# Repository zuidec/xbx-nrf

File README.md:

# XBX-NRF

A replacement bottom board for the **Xbox Series X|S controller (model 1914)**
built on a Nordic **nRF52840**. Uses a custom **2.4 GHz USB dongle** instead of 
Xbox Wireless / Bluetooth for improved connectivity. 

> **Status:** Hardware Rev 1.1 up and running. Still in active development.
> Open tasks: [todo.md](todo.md).

## Who is this for

This is for those of us who love the Xbox controller's shape but hate how bad 
the Bluetooth connectivity is. This started as a labor of love for my partner 
who can't find a controller she likes besides the Xbox controller but also can't 
stand the disconnects.

That being said, there are some real concessions. The most obvious is that the 
controller won't work with an Xbox anymore. Another concession is that support 
for the rechargeable battery packs, as well as the expansion and headphone ports 
was dropped.

- How to build the hardware:
    [Building the hardware](docs/hardware_assembly.md)
- Once you have hardware in hand:
    **[Getting started](docs/getting_started.md)**

## Architecture

```
┌─────────── Controller ───────────┐          ┌──── Dongle ────┐
│ Stock top board ─J3─ new board   │ 2.4 GHz  │ nRF52840 + USB │
│ buttons (PCAL6416)  nRF52840     │◀────────▶│ XInput / HID   │──▶ PC
│ power latch, boost  radio,       │   ESB    │ gamepad        │
│ USB-C, 2×AA input   sticks,      │          │                │
│                     triggers,    │          │                │
│                     rumble       │          │                │
└──────────────────────────────────┘          └────────────────┘
```

## Features

| Area | Feature |
|---|---|
| Target | Xbox Series X\|S Controller (model 1914)|
| Scope | New bottom board, stock top board, shell, triggers, motors reused |
| MCU | nRF52840 |
| Wireless | Nordic ESB 2.4 GHz. The project does **NOT** use Bluetooth! |
| Multiplayer | Up to 7 paired, 4 connected per dongle |
| Polling rate| 1 kHz with 1–2 controllers, 500 Hz with 3–4 |
| Dongle USB mode| HID gamepad (**1 player**) and XInput (**4 players**) |
| Battery | **AAs only** - basic rechargeables are OK, but no Play & Charge |
| Rumble | reuses all the stock motors, including triggers |
| Buttons | reuses stock with additional options for 2 AUX trigger switches and 4 paddles |
| Waking PC | Works in wireless AND wired mode! |
| Audio | None in v1 |
| Expansion port | None in v1 |

> [!WARNING]
> **Never put a bare Li-ion cell on the AA contacts**: The boost converter
> appears to pass that straight through and the nRF52840 is only rated to 
> **3.6v** in this configuration!
> ([docs/hardware.md](docs/hardware.md)).

## Hardware

The custom board replaces the stock bottom board in the controller. It plugs 
into the stock top board's 14-pin **J3** connector. This provides power rails, 
USB, I2C to the button expander, and Guide / Pair / power-hold signals.

| Doc | Covers |
|---|---|
| [docs/hardware.md](docs/hardware.md) | Top board power, J3 pinout, antennas, dongle pin map |
| [docs/pcal6416.md](docs/pcal6416.md) | Button expander: button map, registers |
| [docs/a3910.md](docs/a3910.md) | Rumble drivers: wiring, logic table |
| [docs/teardown.md](docs/teardown.md) | Test controller teardown: motor wires |

## Firmware

Built using the nRF Connect SDK. Version is pinned at v3.4.1 to ensure future 
buildability (hopefully). The controller firmware has a target for the custom 
board and the dongle firmware has a target for the custom dongle as well as the 
PCA10059 dongle. You may notice there is a nice!nano/pro-micro target for the 
controller, but this is just for testing.

| Doc | Covers |
|---|---|
| [docs/controller.md](docs/controller.md) | Using it: power, pairing, LED, wired modes, calibration, waking the PC |
| [docs/building.md](docs/building.md) | Setup; building the firmware, bootloader and configurator; versions |
| [docs/flashing.md](docs/flashing.md) | Flashing and debugging |
| [docs/protocol.md](docs/protocol.md) | Radio (pairing, time slots) and USB (HID, XInput) protocols |
| [docs/gip.md](docs/gip.md) | Xbox GIP protocol notes (optional mode) |

## Configurator

Desktop app for settings, calibration, input and rumble tests and firmware
updates of both devices over USB using Python + Tkinter. So far only tested on 
Linux, but in theory should be buildable on Mac and Windows.

- Getting started:
  [docs/getting_started.md](docs/getting_started.md#setting-up-the-configurator)
- Details: [docs/configurator.md](docs/configurator.md)

## Repository layout

```
docs/                documentation
firmware/
  boards/            our board definitions (xbx_controller, xbx_dongle)
  bootloader/        UF2 bootloader build (upstream + our boards)
  common/            shared code (include/protocol.h)
  xbx-nrf/           controller app
  dongle/            dongle app
  ncs-version        pinned SDK + toolchain
  check-sdk.sh       version check for build.sh
  build.sh           build (+ flash) script
pcb/xbx-nrf/         KiCad project, controller board (lib/: symbols,
                     footprints, 3D)
pcb/xbx-nrf-dongle/  KiCad project, dongle board
mech/                FreeCAD parts: controller-bottom-board/ (board outline),
                     dongle-enclosure/, aux-button-guide/ (CC BY-NC-SA remix)
references/          schematics, scans, datasheets, pinouts
tools/               configurator/, release scripts (pcb-release.sh,
                     release-notices.sh), test-rumble.sh
todo.md              task list
```

## Disclosures

This was built with the help of Claude Code. PCB designs are completely hand 
designed by myself, and all code was either written or reviewed by 
myself. However, there are likely still bugs present as this is a hobbyist 
project in early development. PCB designs may also have flaws for the same 
reasons. If you find and bugs or issues with the hardware, please [open an 
issue](https://github.com/zuidec/xbx-nrf/issues) to let me know.

## References

- Schematics, scans, pinouts and datasheets:
  [references/README.md](references/README.md) (third-party, not in the repo;
  source links there)
- [AcidMods — XB1 controller PCB scans](https://acidmods.com/forum/index.php?topic=44547.120)
- [GP2040-CE](https://github.com/OpenStickCommunity/GP2040-CE) (XInput
  reference)

## License

Copyright (c) 2026 zuidec. Firmware and scripts: **MPL-2.0**. Hardware
design: **CERN-OHL-S-2.0**. Documentation: **CC-BY-4.0**. Third-party CAD
parts (SnapMagic, KiCad libraries) keep their CC-BY-SA-4.0 licenses; see the
`ATTRIBUTION.md` in each library folder. Details: [LICENSE](LICENSE),
[REUSE.toml](REUSE.toml), full texts in [LICENSES/](LICENSES/).

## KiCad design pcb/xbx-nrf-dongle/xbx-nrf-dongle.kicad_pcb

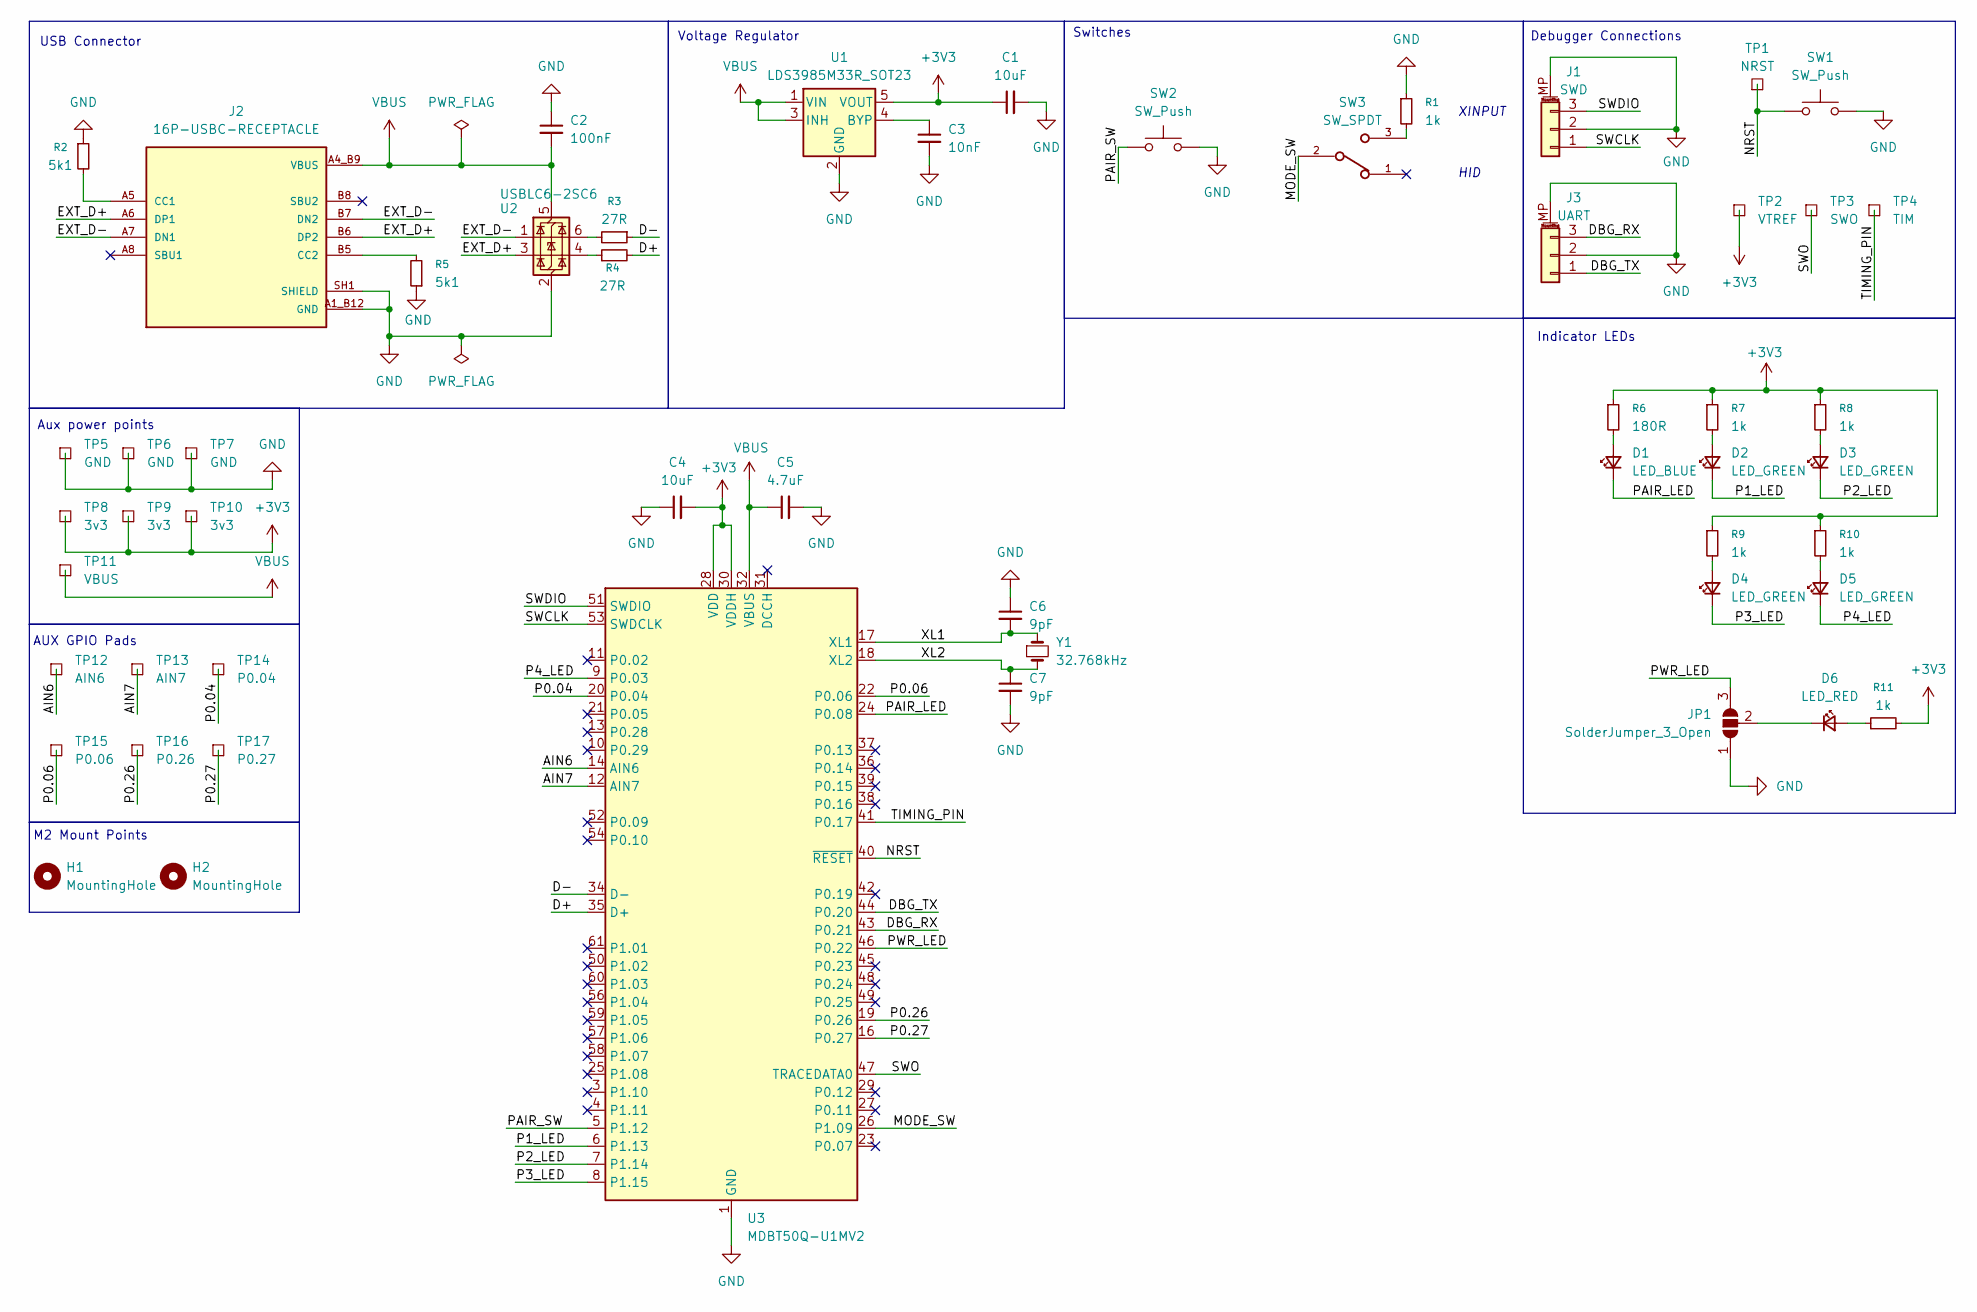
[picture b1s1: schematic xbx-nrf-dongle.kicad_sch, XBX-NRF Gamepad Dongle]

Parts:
C1, C4: 10uF; C_0805_2012Metric_Pad1.18x1.45mm_HandSolder; DigiKey 1276-2402-1-ND
C2: 100nF; C_0603_1608Metric_Pad1.08x0.95mm_HandSolder; DigiKey 399-C0603C104K5RACTUCT-ND
C3: 10nF; C_0603_1608Metric_Pad1.08x0.95mm_HandSolder; DigiKey 399-C0603C103K5RACTUCT-ND
C5: 4.7uF; C_0805_2012Metric_Pad1.18x1.45mm_HandSolder; DigiKey 1276-CL21A475KAQNNNECT-ND
C6, C7: 9pF; C_0603_1608Metric_Pad1.08x0.95mm_HandSolder; DigiKey 399-8728-1-ND
D1: LED_BLUE; LED_0603_1608Metric_Pad1.05x0.95mm_HandSolder; DigiKey 754-1948-1-ND
D2, D3, D4, D5: LED_GREEN; LED_0603_1608Metric_Pad1.05x0.95mm_HandSolder; DigiKey 1080-1582-1-ND
D6: LED_RED; LED_0603_1608Metric_Pad1.05x0.95mm_HandSolder; DigiKey 160-1909-1-ND
H1, H2: MountingHole; MountingHole_2.2mm_M2; DigiKey N/A
J1: SWD; JST_SH_SM03B-SRSS-TB_1x03-1MP_P1.00mm_Horizontal; DigiKey 455-SM03B-SRSS-TBCT-ND
J2: 16P-USBC-RECEPTACLE; USB_C_Receptacle_16P_Amphenol_10155435-00011LF; PARTREV C; DigiKey_Part_Number 609-10155435-00011LFCT-ND
J3: UART; JST_SH_SM03B-SRSS-TB_1x03-1MP_P1.00mm_Horizontal; DigiKey 455-SM03B-SRSS-TBCT-ND
JP1: SolderJumper_3_Open; SolderJumper-3_P2.0mm_Open_TrianglePad1.0x1.5mm_NumberLabels; DigiKey N/A
R1, R7, R8, R9, R10, R11: 1k; R_0603_1608Metric_Pad0.98x0.95mm_HandSolder; DigiKey P1.00KHCT-ND
R2, R5: 5k1; R_0603_1608Metric_Pad0.98x0.95mm_HandSolder; DigiKey P5.10KHCT-ND
R3, R4: 27R; R_0603_1608Metric_Pad0.98x0.95mm_HandSolder; DigiKey 311-27.0HRCT-ND
R6: 180R; R_0603_1608Metric_Pad0.98x0.95mm_HandSolder; DigiKey A129679CT-ND
SW1, SW2: SW_Push; SW_SPST_B3U-1000P; DigiKey 2073-SWT0010-015016SSACT-ND
SW3: SW_SPDT; SW_JS102011SAQN; DigiKey 401-1999-1-ND
TP1: NRST; TestPoint_Pad_1.5x1.5mm-NoSilkscreen; DigiKey N/A
TP2: VTREF; TestPoint_Pad_1.5x1.5mm-NoSilkscreen; DigiKey N/A
TP3: SWO; TestPoint_Pad_1.5x1.5mm-NoSilkscreen; DigiKey N/A
TP4: TIM; TestPoint_Pad_1.5x1.5mm-NoSilkscreen; DigiKey N/A
TP5, TP6, TP7: GND; TestPoint_Pad_1.0x1.0mm-NoSilkscreen; DigiKey N/A
TP8, TP9, TP10: 3v3; TestPoint_Pad_1.0x1.0mm-NoSilkscreen; DigiKey N/A
TP11: VBUS; TestPoint_Pad_1.0x1.0mm-NoSilkscreen; DigiKey N/A
TP12: AIN6; TestPoint_Pad_1.0x1.0mm-NoSilkscreen; DigiKey N/A
TP13: AIN7; TestPoint_Pad_1.0x1.0mm-NoSilkscreen; DigiKey N/A
TP14: P0.04; TestPoint_Pad_1.0x1.0mm-NoSilkscreen; DigiKey N/A
TP15: P0.06; TestPoint_Pad_1.0x1.0mm-NoSilkscreen; DigiKey N/A
TP16: P0.26; TestPoint_Pad_1.0x1.0mm-NoSilkscreen; DigiKey N/A
TP17: P0.27; TestPoint_Pad_1.0x1.0mm-NoSilkscreen; DigiKey N/A
U1: LDS3985M33R_SOT23; SOT-23-5; DigiKey 497-4257-1-ND
U2: USBLC6-2SC6; SOT-23-6; DigiKey 497-5235-1-ND
U3: MDBT50Q-U1MV2; Raytac_MDBT50Q; DigiKey 3271-MDBT50Q-U1MV2-ND
Y1: 32.768kHz; Crystal_SMD_3215-2Pin_3.2x1.5mm; DigiKey 114-FC-13532.7680KA-AG0CT-ND

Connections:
+3V3: C1.1, C4.2, R6.1, R7.1, R8.1, R9.1, R10.1, R11.2, TP2.1 (1_1), TP8.1 (1_1), TP9.1 (1_1), TP10.1 (1_1), U1.5 (VOUT), U3.28 (VDD), U3.30 (VDDH)
/AIN6: TP12.1 (1_1), U3.14 (AIN6)
/AIN7: TP13.1 (1_1), U3.12 (AIN7)
/D+: R4.2, U3.35 (D+)
/D-: R3.1, U3.34 (D-)
/DBG_RX: J3.3, U3.43 (P0.21)
/DBG_TX: J3.1, U3.44 (P0.20)
/EXT_D+: J2.A6 (DP1), J2.B6 (DP2), U2.3 (I/O2)
/EXT_D-: J2.A7 (DN1), J2.B7 (DN2), U2.1 (I/O1)
/MODE_SW: SW3.2, U3.26 (P1.09)
/NRST: SW1.1, TP1.1 (1_1), U3.40 (~RESET)
/P0.04: TP14.1 (1_1), U3.20 (P0.04)
/P0.06: TP15.1 (1_1), U3.22 (P0.06)
/P0.26: TP16.1 (1_1), U3.19 (P0.26)
/P0.27: TP17.1 (1_1), U3.16 (P0.27)
/P1_LED: D2.1 (K), U3.6 (P1.13)
/P2_LED: D3.1 (K), U3.7 (P1.14)
/P3_LED: D4.1 (K), U3.8 (P1.15)
/P4_LED: D5.1 (K), U3.9 (P0.03)
/PAIR_LED: D1.1 (K), U3.24 (P0.08)
/PAIR_SW: SW2.1, U3.5 (P1.12)
/PWR_LED: JP1.3 (B), U3.46 (P0.22)
/SWCLK: J1.1, U3.53 (SWDCLK)
/SWDIO: J1.3, U3.51 (SWDIO)
/SWO: TP3.1 (1_1), U3.47 (TRACEDATA0)
/TIMING_PIN: TP4.1 (1_1), U3.41 (P0.17)
/XL1: C6.2, U3.17 (XL1), Y1.1
/XL2: C7.1, U3.18 (XL2), Y1.2
GND: C1.2, C2.1, C3.2, C4.1, C5.2, C6.1, C7.2, J1.2, J1.MP (MountPin), J2.A1_B12 (GND), J2.B1_A12 (GND), J2.SH1 (SHIELD), J2.SH2 (SHIELD), J2.SH3 (SHIELD), J2.SH4 (SHIELD), J3.2, J3.MP (MountPin), JP1.1 (A), R1.1, R2.1, R5.1, SW1.2, SW2.2, TP5.1 (1_1), TP6.1 (1_1), TP7.1 (1_1), U1.2 (GND), U2.2 (GND), U3.1 (GND), U3.2 (GND), U3.15 (GND), U3.33 (GND), U3.55 (GND)
unnamed: D1.2 (A), R6.2
unnamed: D2.2 (A), R7.2
unnamed: D3.2 (A), R8.2
unnamed: D4.2 (A), R9.2
unnamed: D5.2 (A), R10.2
unnamed: D6.2 (A), R11.1
unnamed: D6.1 (K), JP1.2 (C)
unnamed: J2.A5 (CC1), R2.2
unnamed: J2.B5 (CC2), R5.2
unnamed: R1.2, SW3.3
unnamed: R3.2, U2.6 (I/O1)
unnamed: R4.1, U2.4 (I/O2)
unnamed: C3.1, U1.4 (BYP)
VBUS: C2.2, C5.1, J2.A4_B9 (VBUS), J2.B4_A9 (VBUS), TP11.1 (1_1), U1.1 (VIN), U1.3 (INH), U2.5 (VBUS), U3.32 (VBUS)

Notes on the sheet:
XINPUT
Voltage Regulator
Aux power points
Debugger Connections
HID
AUX GPIO Pads
M2 Mount Points
Indicator LEDs
USB Connector
Switches

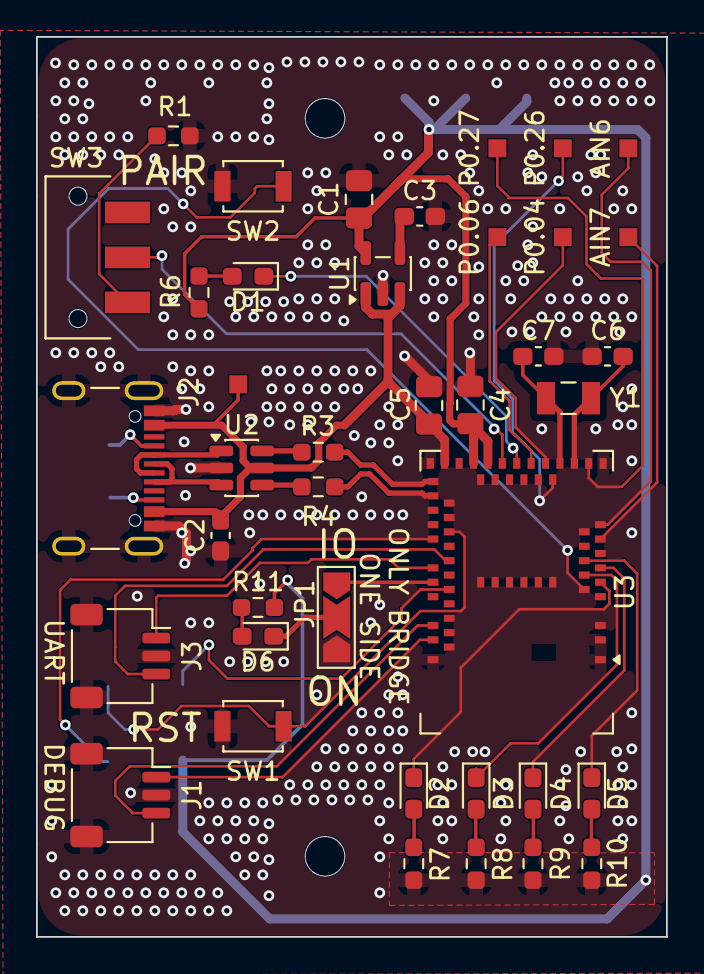
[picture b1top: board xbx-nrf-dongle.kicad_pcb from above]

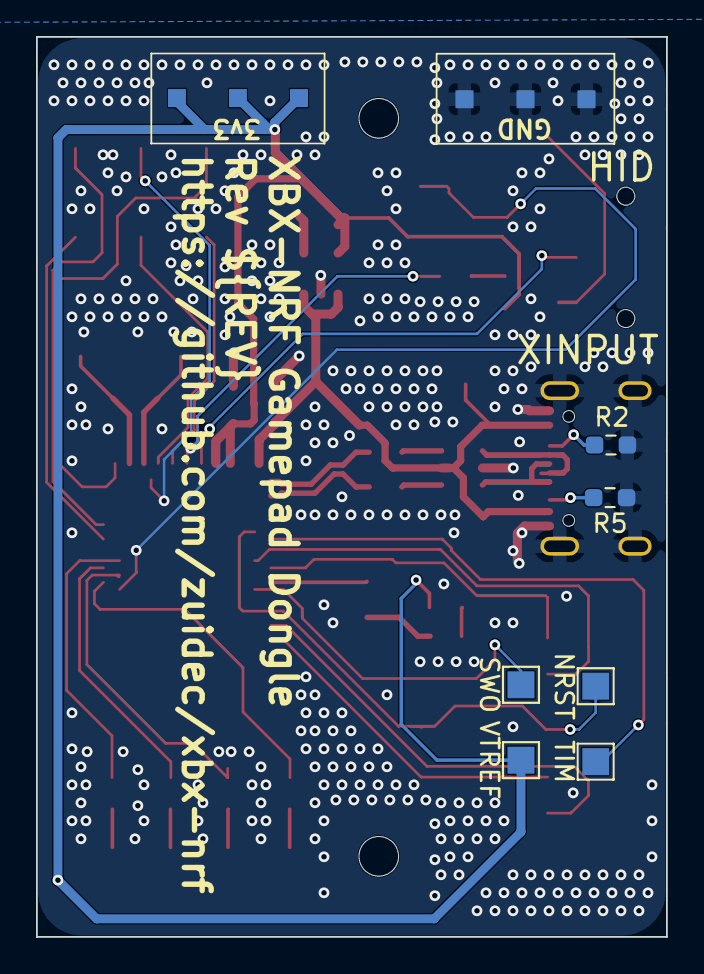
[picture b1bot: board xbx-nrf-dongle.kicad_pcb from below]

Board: 2 copper layers, 35.0 x 50.0 mm, 54 parts (12 on the bottom side), 43 nets.

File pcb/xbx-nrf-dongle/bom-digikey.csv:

Designator,Qty,Value,Footprint,Manufacturer,MPN,DigiKey,Notes
"C1, C4",2,10uF,0805,Samsung,CL21A106KPCLQNC,1276-2402-1-ND,
C2,1,100nF,0603,KEMET,C0603C104K5RACTU,399-C0603C104K5RACTUCT-ND,
C3,1,10nF,0603,KEMET,C0603C103K5RACTU,399-C0603C103K5RACTUCT-ND,
C5,1,4.7uF,0805,Samsung,CL21A475KAQNNNE,1276-CL21A475KAQNNNECT-ND,
"C6, C7",2,9pF,0603,KEMET,CBR06C909BAGAC,399-8728-1-ND,
D1,1,LED blue,0603,Kingbright,APTD1608LVBC/D,754-1948-1-ND,
"D2, D3, D4, D5",4,LED green,0603,Everlight,19-213SYGW/S5888/TR8,1080-1582-1-ND,
D6,1,LED red,0603,Lite-On,LTST-C193KRKT-2A,160-1909-1-ND,
"J1, J3",2,SWD / UART,JST SH 3-pin R/A,JST,SM03B-SRSS-TB,455-SM03B-SRSS-TBCT-ND,
J2,1,USB-C receptacle,16-pin,Amphenol,10155435-00011LF,609-10155435-00011LFCT-ND,
"R1, R7, R8, R9, R10, R11",6,1k,0603,Panasonic,ERJ-3EKF1001V,P1.00KHCT-ND,
"R2, R5",2,5k1,0603,Panasonic,ERJ-3EKF5101V,P5.10KHCT-ND,
"R3, R4",2,27R,0603,YAGEO,RC0603FR-0727RL,311-27.0HRCT-ND,
R6,1,180R,0603,TE Connectivity,CRGCQ0603F180R,A129679CT-ND,
"SW1, SW2",2,Reset / Pair,B3U-1000P,GCT,SWT0010-015016SSA,2073-SWT0010-015016SSACT-ND,
SW3,1,Mode (SPDT slide),JS102011SAQN,C&K,JS102011SAQN,401-1999-1-ND,
U1,1,LDS3985M33R,SOT-23-5,STMicroelectronics,LDS3985M33R,497-4257-1-ND,
U2,1,USBLC6-2SC6,SOT-23-6,STMicroelectronics,USBLC6-2SC6,497-5235-1-ND,
U3,1,MDBT50Q-U1MV2,Raytac MDBT50Q,Raytac,MDBT50Q-U1MV2,3271-MDBT50Q-U1MV2-ND,u.FL version
Y1,1,32.768kHz,3.2x1.5 mm,Epson,FC-135 32.7680KA-AG0,114-FC-13532.7680KA-AG0CT-ND,
-,1,Antenna (FPC u.FL),,KYOCERA AVX,1003893FT-AA10L0050,478-1003893FT-AA10L0050-ND,

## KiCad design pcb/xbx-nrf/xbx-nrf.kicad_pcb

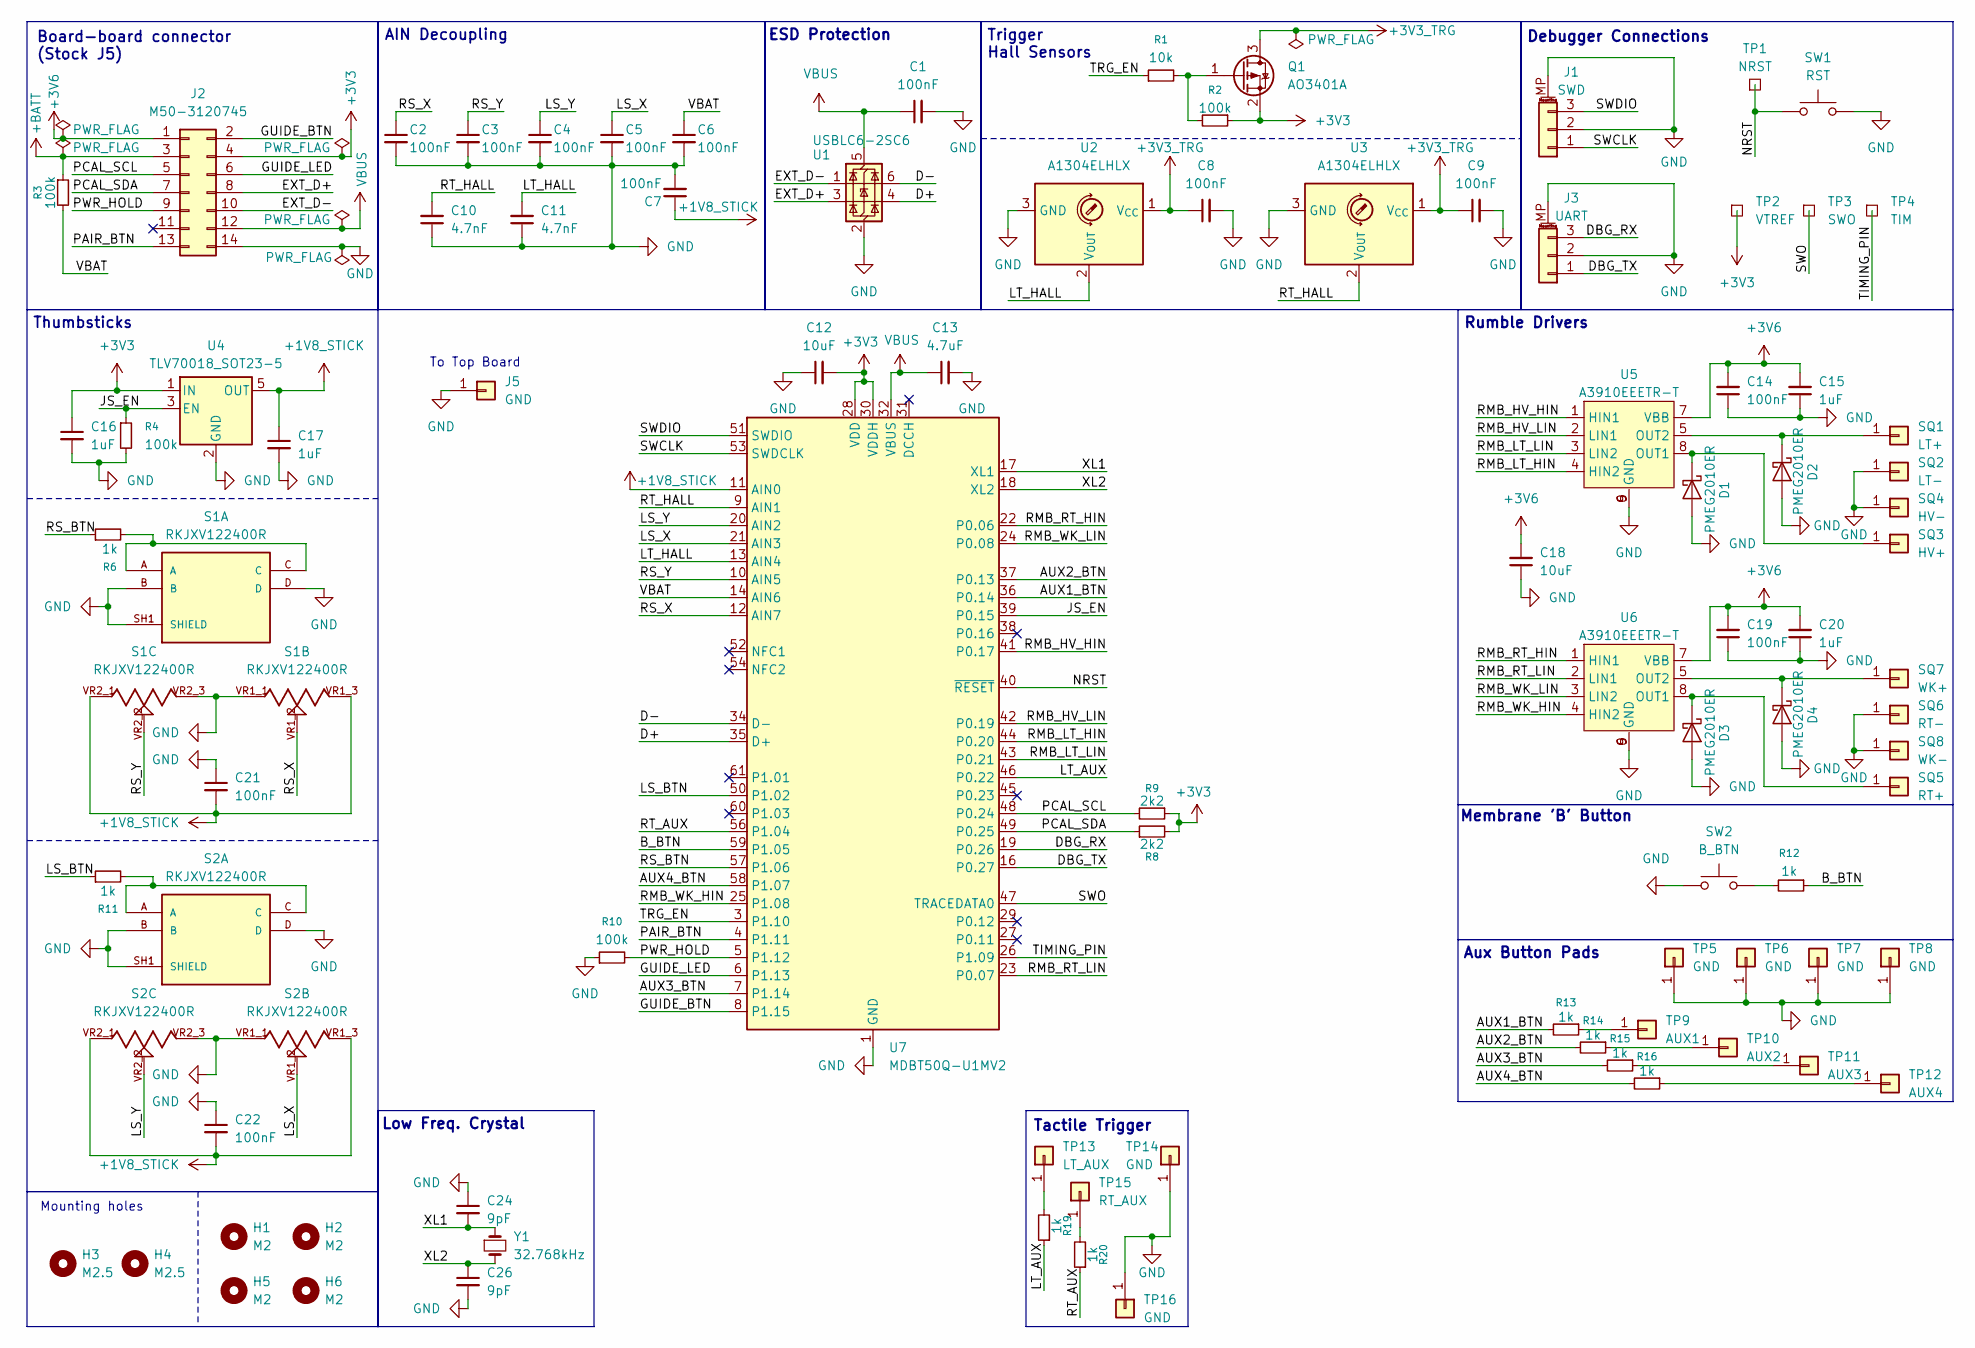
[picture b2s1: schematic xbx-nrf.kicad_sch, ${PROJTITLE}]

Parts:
C1, C2, C3, C4, C5, C6, C7, C8, C9, C14, C19, C21, C22: 100nF; C_0603_1608Metric_Pad1.08x0.95mm_HandSolder; DigiKey 399-C0603C104K5RACTUCT-ND
C10, C11: 4.7nF; C_0603_1608Metric_Pad1.08x0.95mm_HandSolder; DigiKey 399-C0603C472J5RACTUCT-ND
C12, C18: 10uF; C_0805_2012Metric_Pad1.18x1.45mm_HandSolder; DigiKey 1276-2402-1-ND
C13: 4.7uF; C_0805_2012Metric_Pad1.18x1.45mm_HandSolder; DigiKey 1276-CL21A475KAQNNNECT-ND
C15, C16, C17, C20: 1uF; C_0603_1608Metric_Pad1.08x0.95mm_HandSolder; DigiKey 399-C0603C105K4RACTUCT-ND
C24, C26: 9pF; C_0603_1608Metric_Pad1.08x0.95mm_HandSolder; DigiKey 399-8728-1-ND
D1, D2, D3, D4: PMEG2010ER; Nexperia_CFP3_SOD-123W; DigiKey 1727-PMEG2010ER-QXCT-ND
H1, H2, H5, H6: M2; MountingHole_2.2mm_M2; DigiKey N/A
H3, H4: M2.5; MountingHole_2.7mm_M2.5; DigiKey N/A
J1: SWD; JST_SH_SM03B-SRSS-TB_1x03-1MP_P1.00mm_Horizontal; DigiKey 455-SM03B-SRSS-TBCT-ND
J2: M50-3120745; PinSocket_2x07_P1.27mm_Vertical_SMD; DigiKey M50-3120745-ND
J3: UART; JST_SH_SM03B-SRSS-TB_1x03-1MP_P1.00mm_Horizontal; DigiKey 455-SM03B-SRSS-TBCT-ND
J5: GND; SolderWirePad_1x01_SMD_1.5x3mm; DigiKey N/A
Q1: AO3401A; SOT-23; DigiKey 785-1001-1-ND
R1: 10k; R_0603_1608Metric_Pad0.98x0.95mm_HandSolder; DigiKey 311-10.0KHRCT-ND
R2, R3, R4, R10: 100k; R_0603_1608Metric_Pad0.98x0.95mm_HandSolder; DigiKey 541-100KHCT-ND
R6, R11, R12, R13, R14, R15, R16, R19, R20: 1k; R_0603_1608Metric_Pad0.98x0.95mm_HandSolder; DigiKey P1.00KHCT-ND
R8, R9: 2k2; R_0603_1608Metric_Pad0.98x0.95mm_HandSolder; DigiKey 311-2.20KHRCT-ND
S1, S2: RKJXV122400R; SW_RKJXV122400R; PARTREV N/A; DigiKey N/A
SQ1: LT+; SolderWirePad_1x01_SMD_1.5x3mm; DigiKey N/A
SQ2: LT-; SolderWirePad_1x01_SMD_1.5x3mm; DigiKey N/A
SQ3: HV+; SolderWirePad_1x01_SMD_1.5x3mm; DigiKey N/A
SQ4: HV-; SolderWirePad_1x01_SMD_1.5x3mm; DigiKey N/A
SQ5: RT+; SolderWirePad_1x01_SMD_1.5x3mm; DigiKey N/A
SQ6: RT-; SolderWirePad_1x01_SMD_1.5x3mm; DigiKey N/A
SQ7: WK+; SolderWirePad_1x01_SMD_1.5x3mm; DigiKey N/A
SQ8: WK-; SolderWirePad_1x01_SMD_1.5x3mm; DigiKey N/A
SW1: RST; SW_SPST_B3U-1000P; DigiKey 2073-SWT0010-015016SSACT-ND
SW2: B_BTN; Membrane_Contact_D8.0mm_Interdigitated; DigiKey N/A
TP1: NRST; TestPoint_Pad_1.5x1.5mm-BigSilkscreen; DigiKey N/A
TP2: VTREF; TestPoint_Pad_1.5x1.5mm-BigSilkscreen; DigiKey N/A
TP3: SWO; TestPoint_Pad_1.5x1.5mm-BigSilkscreen; DigiKey N/A
TP4: TIM; TestPoint_Pad_1.5x1.5mm-BigSilkscreen; DigiKey N/A
TP5, TP6, TP7, TP8, TP14, TP16: GND; SolderWirePad_1x01_SMD_1x2mm; DigiKey N/A
TP9: AUX1; SolderWirePad_1x01_SMD_1x2mm; DigiKey N/A
TP10: AUX2; SolderWirePad_1x01_SMD_1x2mm; DigiKey N/A
TP11: AUX3; SolderWirePad_1x01_SMD_1x2mm; DigiKey N/A
TP12: AUX4; SolderWirePad_1x01_SMD_1x2mm; DigiKey N/A
TP13: LT_AUX; SolderWirePad_1x01_SMD_1x2mm; DigiKey N/A
TP15: RT_AUX; SolderWirePad_1x01_SMD_1x2mm; DigiKey N/A
U1: USBLC6-2SC6; SOT-23-6; DigiKey 497-5235-1-ND
U2, U3: A1304ELHLX; SOT-23W; DigiKey 620-1548-1-ND
U4: TLV70018_SOT23-5; SOT-23-5; DigiKey 296-32410-1-ND
U5, U6: A3910EEETR-T; DFN-8-1EP_2x2mm_P0.5mm_EP0.9x1.6mm; DigiKey 620-1495-1-ND
U7: MDBT50Q-U1MV2; Raytac_MDBT50Q; DigiKey 3271-MDBT50Q-U1MV2-ND
Y1: 32.768kHz; Crystal_SMD_3215-2Pin_3.2x1.5mm; DigiKey 114-FC-13532.7680KA-AG0CT-ND

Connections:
+1V8_STICK: C7.1, C17.1, C21.2, C22.2, S1.VR1_3, S1.VR2_1, S2.VR1_3, S2.VR2_1, U4.5 (OUT), U7.11 (AIN0)
+3V3: C12.2, C16.1, J2.4, Q1.2 (S), R2.1, R8.2, R9.1, TP2.1 (1_1), U4.1 (IN), U7.28 (VDD), U7.30 (VDDH)
+3V3_TRG: C8.1, C9.1, Q1.3 (D), U2.1 (V_{CC}), U3.1 (V_{CC})
+3V6: C14.2, C15.2, C18.2, C19.2, C20.2, J2.1, U5.7 (VBB), U6.7 (VBB)
+BATT: J2.3, R3.1
/AUX1_BTN: R13.2, U7.36 (P0.14)
/AUX2_BTN: R14.2, U7.37 (P0.13)
/AUX3_BTN: R15.2, U7.7 (P1.14)
/AUX4_BTN: R16.2, U7.58 (P1.07)
/B_BTN: R12.1, U7.59 (P1.05)
/D+: U1.4 (I/O2), U7.35 (D+)
/D-: U1.6 (I/O1), U7.34 (D-)
/DBG_RX: J3.3, U7.19 (P0.26)
/DBG_TX: J3.1, U7.16 (P0.27)
/EXT_D+: J2.8, U1.3 (I/O2)
/EXT_D-: J2.10, U1.1 (I/O1)
/GUIDE_BTN: J2.2, U7.8 (P1.15)
/GUIDE_LED: J2.6, U7.6 (P1.13)
/JS_EN: R4.1, U4.3 (EN), U7.39 (P0.15)
/LS_BTN: R11.1, U7.50 (P1.02)
/LS_X: C5.1, S2.VR1_2, U7.21 (AIN3)
/LS_Y: C4.1, S2.VR2_2, U7.20 (AIN2)
/LT_AUX: R19.1, U7.46 (P0.22)
/LT_HALL: C11.2, U2.2 (V_{OUT}), U7.13 (AIN4)
/NRST: SW1.1, TP1.1 (1_1), U7.40 (~RESET)
/PAIR_BTN: J2.13, U7.4 (P1.11)
/PCAL_SCL: J2.5, R9.2, U7.48 (P0.24)
/PCAL_SDA: J2.7, R8.1, U7.49 (P0.25)
/PWR_HOLD: J2.9, R10.2, U7.5 (P1.12)
/RMB_HV_HIN: U5.1 (HIN1), U7.41 (P0.17)
/RMB_HV_LIN: U5.2 (LIN1), U7.42 (P0.19)
/RMB_LT_HIN: U5.4 (HIN2), U7.44 (P0.20)
/RMB_LT_LIN: U5.3 (LIN2), U7.43 (P0.21)
/RMB_RT_HIN: U6.1 (HIN1), U7.22 (P0.06)
/RMB_RT_LIN: U6.2 (LIN1), U7.23 (P0.07)
/RMB_WK_HIN: U6.4 (HIN2), U7.25 (P1.08)
/RMB_WK_LIN: U6.3 (LIN2), U7.24 (P0.08)
/RS_BTN: R6.1, U7.57 (P1.06)
/RS_X: C2.1, S1.VR1_2, U7.12 (AIN7)
/RS_Y: C3.1, S1.VR2_2, U7.10 (AIN5)
/RT_AUX: R20.1, U7.56 (P1.04)
/RT_HALL: C10.2, U3.2 (V_{OUT}), U7.9 (AIN1)
/SWCLK: J1.1, U7.53 (SWDCLK)
/SWDIO: J1.3, U7.51 (SWDIO)
/SWO: TP3.1 (1_1), U7.47 (TRACEDATA0)
/TIMING_PIN: TP4.1 (1_1), U7.26 (P1.09)
/TRG_EN: R1.1, U7.3 (P1.10)
/VBAT: C6.1, R3.2, U7.14 (AIN6)
/XL1: C24.2, U7.17 (XL1), Y1.1
/XL2: C26.1, U7.18 (XL2), Y1.2
GND: C1.2, C2.2, C3.2, C4.2, C5.2, C6.2, C7.2, C8.2, C9.2, C10.1, C11.1, C12.1, C13.2, C14.1, C15.1, C16.2, C17.2, C18.1, C19.1, C20.1, C21.1, C22.1, C24.1, C26.2, D1.2 (A), D2.2 (A), D3.2 (A), D4.2 (A), J1.2, J1.MP (MountPin), J2.14, J3.2, J3.MP (MountPin), J5.1 (Pin_1_1), R4.2, R10.1, S1.B, S1.D, S1.SH1 (SHIELD), S1.SH2 (SHIELD), S1.SH3 (SHIELD), S1.SH4 (SHIELD), S1.VR1_1, S1.VR2_3, S2.B, S2.D, S2.SH1 (SHIELD), S2.SH2 (SHIELD), S2.SH3 (SHIELD), S2.SH4 (SHIELD), S2.VR1_1, S2.VR2_3, SQ2.1 (Pin_1_1), SQ4.1 (Pin_1_1), SQ6.1 (Pin_1_1), SQ8.1 (Pin_1_1), SW1.2, SW2.1, TP5.1 (Pin_1_1), TP6.1 (Pin_1_1), TP7.1 (Pin_1_1), TP8.1 (Pin_1_1), TP14.1 (Pin_1_1), TP16.1 (Pin_1_1), U1.2 (GND), U2.3 (GND), U3.3 (GND), U4.2 (GND), U5.6 (GND), U5.9 (GND), U6.6 (GND), U6.9 (GND), U7.1 (GND), U7.2 (GND), U7.15 (GND), U7.33 (GND), U7.55 (GND)
unnamed: D1.1 (K), SQ3.1 (Pin_1_1), U5.8 (OUT1)
unnamed: D2.1 (K), SQ1.1 (Pin_1_1), U5.5 (OUT2)
unnamed: D3.1 (K), SQ5.1 (Pin_1_1), U6.8 (OUT1)
unnamed: D4.1 (K), SQ7.1 (Pin_1_1), U6.5 (OUT2)
unnamed: Q1.1 (G), R1.2, R2.2
unnamed: R6.2, S1.A, S1.C
unnamed: R11.2, S2.A, S2.C
unnamed: R12.2, SW2.2
unnamed: R13.1, TP9.1 (Pin_1_1)
unnamed: R14.1, TP10.1 (Pin_1_1)
unnamed: R15.1, TP11.1 (Pin_1_1)
unnamed: R16.1, TP12.1 (Pin_1_1)
unnamed: R19.2, TP13.1 (Pin_1_1)
unnamed: R20.2, TP15.1 (Pin_1_1)
VBUS: C1.1, C13.1, J2.12, U1.5 (VBUS), U7.32 (VBUS)

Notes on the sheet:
Mounting holes
Tactile Trigger
Rumble Drivers
To Top Board
Debugger Connections
Membrane 'B' Button
Thumbsticks
ESD Protection
Aux Button Pads
Board-board connector (Stock J5)
AIN Decoupling
Trigger Hall Sensors
Low Freq. Crystal

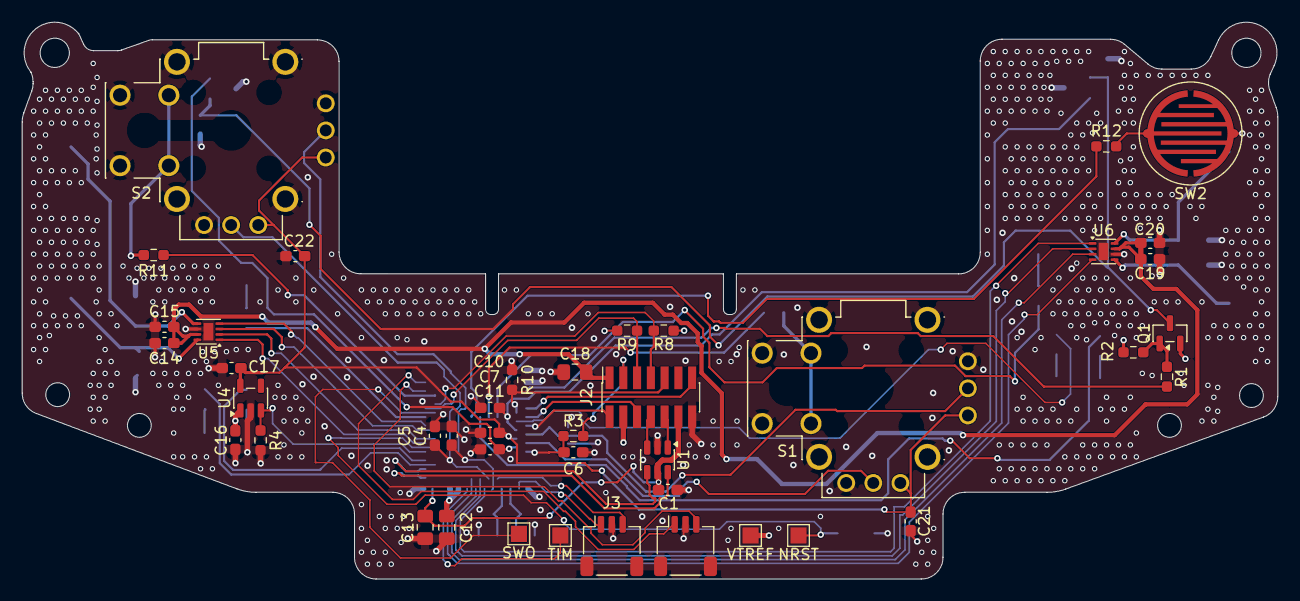
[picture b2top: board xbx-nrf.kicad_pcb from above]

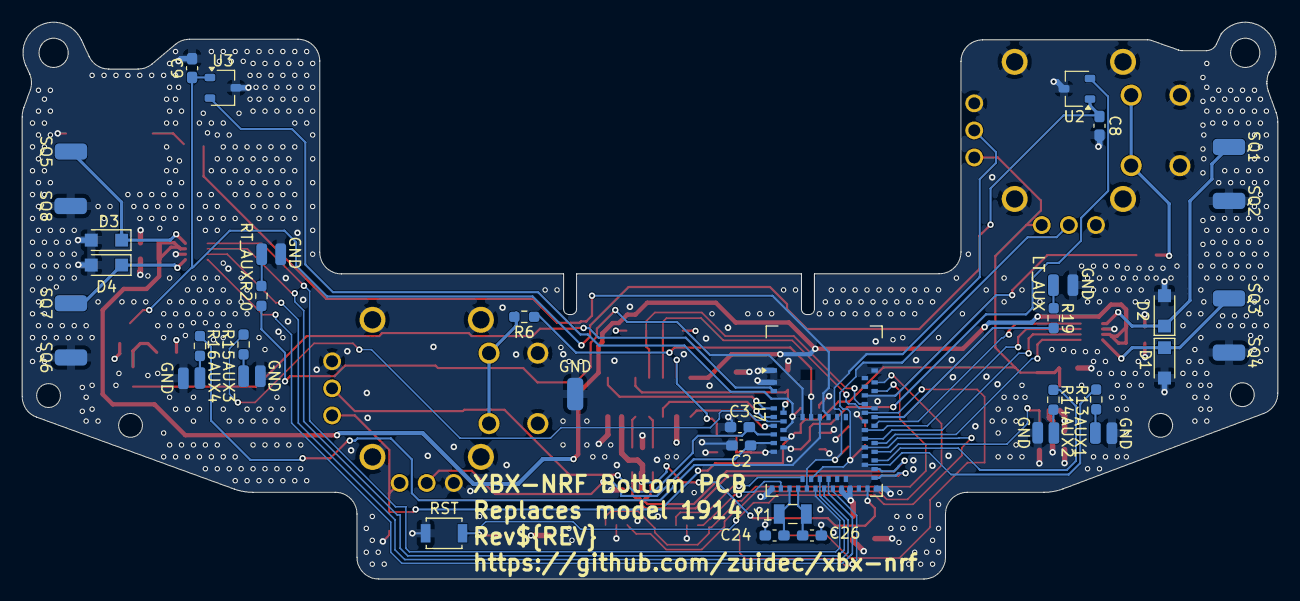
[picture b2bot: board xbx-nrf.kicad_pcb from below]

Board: 4 copper layers, 115.8 x 51.4 mm, 91 parts (43 on the bottom side), 66 nets.

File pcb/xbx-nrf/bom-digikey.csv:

Designator,Qty,Value,Footprint,Manufacturer,MPN,DigiKey,Notes
"C1, C2, C3, C4, C5, C6, C7, C8, C9, C14, C19, C21, C22",13,100nF,0603,KEMET,C0603C104K5RACTU,399-C0603C104K5RACTUCT-ND,
"C10, C11",2,4.7nF,0603,KEMET,C0603C472J5RACTU,399-C0603C472J5RACTUCT-ND,
"C12, C18",2,10uF,0805,Samsung,CL21A106KPCLQNC,1276-2402-1-ND,
C13,1,4.7uF,0805,Samsung,CL21A475KAQNNNE,1276-CL21A475KAQNNNECT-ND,
"C15, C16, C17, C20",4,1uF,0603,KEMET,C0603C105K4RACTU,399-C0603C105K4RACTUCT-ND,
"C24, C26",2,9pF,0603,KEMET,CBR06C909BAGAC,399-8728-1-ND,
"D1, D2, D3, D4",4,PMEG2010ER,SOD-123W,Nexperia,PMEG2010ER-QX,1727-PMEG2010ER-QXCT-ND,
"J1, J3",2,SWD / UART,JST SH 3-pin R/A,JST,SM03B-SRSS-TB,455-SM03B-SRSS-TBCT-ND,
J2,1,M50-3120745,2x7 1.27 mm socket,Harwin,M50-3120745,M50-3120745-ND,Or reuse the stock J5; file pin 1 corner (see the assembly doc)
Q1,1,AO3401A,SOT-23,Alpha & Omega,AO3401A,785-1001-1-ND,
R1,1,10k,0603,YAGEO,RC0603FR-0710KL,311-10.0KHRCT-ND,
"R2, R3, R4, R10",4,100k,0603,Vishay Dale,CRCW0603100KFKEA,541-100KHCT-ND,
"R6, R11, R12, R13, R14, R15, R16, R19, R20",9,1k,0603,Panasonic,ERJ-3EKF1001V,P1.00KHCT-ND,
"R8, R9",2,2k2,0603,YAGEO,RC0603FR-072K2L,311-2.20KHRCT-ND,
"S1, S2",2,Analog stick,Alps RKJXV,,,N/A,Reuse the stock sticks; any Series X|S stick fits
SW1,1,Reset,B3U-1000P,GCT,SWT0010-015016SSA,2073-SWT0010-015016SSACT-ND,
U1,1,USBLC6-2SC6,SOT-23-6,STMicroelectronics,USBLC6-2SC6,497-5235-1-ND,
"U2, U3",2,A1304ELHLX,SOT-23W,Allegro,A1304ELHLX-T,620-1548-1-ND,Or reuse stock U10/U11
U4,1,TLV70018,SOT-23-5,Texas Instruments,TLV70018DDCR,296-32410-1-ND,
"U5, U6",2,A3910,DFN-8 2x2 mm,Allegro,A3910EEETR-T,620-1495-1-ND,Or reuse stock U4/U5
U7,1,MDBT50Q-U1MV2,Raytac MDBT50Q,Raytac,MDBT50Q-U1MV2,3271-MDBT50Q-U1MV2-ND,u.FL version
Y1,1,32.768kHz,3.2x1.5 mm,Epson,FC-135 32.7680KA-AG0,114-FC-13532.7680KA-AG0CT-ND,
-,1,u.FL coax pigtail,,,,N/A,To the top board antenna (see the assembly doc)

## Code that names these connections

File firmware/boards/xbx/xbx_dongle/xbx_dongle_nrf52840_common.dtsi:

/*
 * xbx-nrf dongle, Rev1 (pcb/xbx-nrf-dongle/), shared by both variants. Raytac
 * MDBT50Q-U1MV2 in normal voltage mode: VDD and VDDH from a 3.3 V LDO, so
 * REG0 is unused. The module
 * carries the REG1 DC/DC inductors. LEDs sink to their GPIO (active low),
 * so their PWM pins are open-drain: "off" floats the pin instead of driving
 * it high.
 */

#include <nordic/nrf52840_qiaa.dtsi>
#include "xbx_dongle_nrf52840-pinctrl.dtsi"
#include <zephyr/dt-bindings/input/input-event-codes.h>
#include <zephyr/dt-bindings/gpio/nordic-nrf-gpio.h>

/ {
	model = "xbx-nrf dongle";
	compatible = "xbx-nrf,dongle";

	chosen {
		zephyr,sram = &sram0;
		zephyr,flash = &flash0;
		zephyr,console = &uart0;
		zephyr,shell-uart = &uart0;
	};

	/* 1 ms period; brightness from the configurator (leds.c) */
	pwmleds {
		compatible = "pwm-leds";

		/* blue, 180 Ω: high drive (low side) */
		pair_led: pair_led {
			pwms = <&pwm1 0 PWM_MSEC(1) PWM_POLARITY_INVERTED>;
			label = "PAIR_LED (blue)";
		};

		p1_led: p1_led {
			pwms = <&pwm0 0 PWM_MSEC(1) PWM_POLARITY_INVERTED>;
			label = "P1_LED (green)";
		};

		p2_led: p2_led {
			pwms = <&pwm0 1 PWM_MSEC(1) PWM_POLARITY_INVERTED>;
			label = "P2_LED (green)";
		};

		p3_led: p3_led {
			pwms = <&pwm0 2 PWM_MSEC(1) PWM_POLARITY_INVERTED>;
			label = "P3_LED (green)";
		};

		p4_led: p4_led {
			pwms = <&pwm0 3 PWM_MSEC(1) PWM_POLARITY_INVERTED>;
			label = "P4_LED (green)";
		};

		/* only with JP1 2–3 bridged (pinctrl: why open-drain matters here) */
		pwr_led: pwr_led {
			pwms = <&pwm1 1 PWM_MSEC(1) PWM_POLARITY_INVERTED>;
			label = "PWR_LED (red)";
		};
	};

	buttons {
		compatible = "gpio-keys";

		pair_sw: pair_sw {
			gpios = <&gpio1 12 (GPIO_PULL_UP | GPIO_ACTIVE_LOW)>;
			label = "PAIR_SW";
			zephyr,code = <INPUT_KEY_0>;
		};
	};

	aliases {
		sw0 = &pair_sw;
		pwm-led0 = &pair_led;
		pwm-led1 = &p1_led;
		pwm-led2 = &p2_led;
		pwm-led3 = &p3_led;
		pwm-led4 = &p4_led;
		pwm-led5 = &pwr_led;
		watchdog0 = &wdt0;
	};
};

&reg1 {
	regulator-initial-mode = <NRF5X_REG_MODE_DCDC>;
};

&uicr {
	gpio-as-nreset;
};

&adc {
	status = "okay";
};

&pwm0 {
	status = "okay";
	pinctrl-0 = <&pwm0_default>;
	pinctrl-1 = <&pwm0_sleep>;
	pinctrl-names = "default", "sleep";
};

&pwm1 {
	status = "okay";
	pinctrl-0 = <&pwm1_default>;
	pinctrl-1 = <&pwm1_sleep>;
	pinctrl-names = "default", "sleep";
};

&gpiote {
	status = "okay";
};

&gpio0 {
	status = "okay";
};

&gpio1 {
	status = "okay";
};

&uart0 {
	compatible = "nordic,nrf-uarte";
	status = "okay";
	current-speed = <115200>;
	pinctrl-0 = <&uart0_default>;
	pinctrl-1 = <&uart0_sleep>;
	pinctrl-names = "default", "sleep";
};

zephyr_udc0: &usbd {
	compatible = "nordic,nrf-usbd";
	status = "okay";
};

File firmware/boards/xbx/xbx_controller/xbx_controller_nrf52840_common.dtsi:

/*
 * xbx-nrf controller bottom board, Rev1.1 (pcb/xbx-nrf/), shared by both
 * variants. Raytac MDBT50Q-U1MV2 on the top board's 3.3 V (J2 pin 4), normal
 * voltage mode: REG0 is unused, the module carries the REG1 DC/DC inductors.
 *
 * PWR_HOLD (J2 pin 9) is raised as soon as the GPIO driver starts: on AAs the
 * top board only keeps 3.3 V up while Guide or Pair is held. It also takes
 * the PCAL6416 out of reset (R10 pulls it low). The app releases it to power
 * off.
 */

#include <nordic/nrf52840_qiaa.dtsi>
#include "xbx_controller_nrf52840-pinctrl.dtsi"
#include <zephyr/dt-bindings/input/input-event-codes.h>
#include <zephyr/dt-bindings/gpio/nordic-nrf-gpio.h>
#include <zephyr/dt-bindings/pwm/pwm.h>

/ {
	model = "xbx-nrf controller";
	compatible = "xbx-nrf,controller";

	chosen {
		zephyr,sram = &sram0;
		zephyr,flash = &flash0;
		zephyr,console = &uart0;
		zephyr,shell-uart = &uart0;
	};

	pwmleds {
		compatible = "pwm-leds";

		/* drives Q3 on the top board; polarity not verified */
		guide_led: guide_led {
			pwms = <&pwm0 0 PWM_MSEC(1) PWM_POLARITY_NORMAL>;
			label = "GUIDE_LED";
		};
	};

	/*
	 * No pull-ups on the board: Guide and Pair come from the top board
	 * through diodes (D27, D30), the others switch to GND through 1 kΩ.
	 */
	buttons {
		compatible = "gpio-keys";

		guide_btn: guide_btn {
			gpios = <&gpio1 15 (GPIO_PULL_UP | GPIO_ACTIVE_LOW)>;
			label = "GUIDE_BTN";
			zephyr,code = <INPUT_BTN_MODE>;
		};

		pair_btn: pair_btn {
			gpios = <&gpio1 11 (GPIO_PULL_UP | GPIO_ACTIVE_LOW)>;
			label = "PAIR_BTN";
			zephyr,code = <INPUT_KEY_0>;
		};

		b_btn: b_btn {
			gpios = <&gpio1 5 (GPIO_PULL_UP | GPIO_ACTIVE_LOW)>;
			label = "B_BTN";
			zephyr,code = <INPUT_BTN_EAST>;
		};

		ls_btn: ls_btn {
			gpios = <&gpio1 2 (GPIO_PULL_UP | GPIO_ACTIVE_LOW)>;
			label = "LS_BTN";
			zephyr,code = <INPUT_BTN_THUMBL>;
		};

		rs_btn: rs_btn {
			gpios = <&gpio1 6 (GPIO_PULL_UP | GPIO_ACTIVE_LOW)>;
			label = "RS_BTN";
			zephyr,code = <INPUT_BTN_THUMBR>;
		};
	};

	aliases {
		sw0 = &pair_btn;
		led0 = &guide_led;
		pwm-led0 = &guide_led;
		watchdog0 = &wdt0;
	};
};

&reg1 {
	regulator-initial-mode = <NRF5X_REG_MODE_DCDC>;
};

&uicr {
	gpio-as-nreset;
};

&adc {
	status = "okay";
};

&gpiote {
	status = "okay";
};

&gpio0 {
	status = "okay";
};

&gpio1 {
	status = "okay";

	pwr_hold: pwr_hold {
		gpio-hog;
		gpios = <12 GPIO_ACTIVE_HIGH>;
		output-high;
		line-name = "PWR_HOLD";
	};
};

&uart0 {
	compatible = "nordic,nrf-uarte";
	status = "okay";
	current-speed = <115200>;
	pinctrl-0 = <&uart0_default>;
	pinctrl-1 = <&uart0_sleep>;
	pinctrl-names = "default", "sleep";
};

&i2c0 {
	compatible = "nordic,nrf-twim";
	status = "okay";
	clock-frequency = <I2C_BITRATE_FAST>;
	pinctrl-0 = <&i2c0_default>;
	pinctrl-1 = <&i2c0_sleep>;
	pinctrl-names = "default", "sleep";

	/* top board U4: most buttons; reset = PWR_HOLD, no interrupt line */
	pcal6416: gpio@21 {
		compatible = "nxp,pcal6416a";
		reg = <0x21>;
		gpio-controller;
		#gpio-cells = <2>;
		ngpios = <16>;
	};
};

&pwm0 {
	status = "okay";
	pinctrl-0 = <&pwm0_default>;
	pinctrl-1 = <&pwm0_sleep>;
	pinctrl-names = "default", "sleep";
};

/* rumble motor HIN pins (A3910 U5, U6) */
&pwm1 {
	status = "okay";
	pinctrl-0 = <&pwm1_default>;
	pinctrl-1 = <&pwm1_sleep>;
	pinctrl-names = "default", "sleep";
};

zephyr_udc0: &usbd {
	compatible = "nordic,nrf-usbd";
	status = "okay";
};
